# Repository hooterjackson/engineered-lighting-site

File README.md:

# Engineered Lighting · Engineering Notebook

The prototype series for the Engineered Lighting robotic spotlight — research,
bench builds, perception stack, and software — published as a book-style site.

**Live site:** <https://hooterjackson.github.io/engineered-lighting-site/>
(moving to <https://engineering.engineered.lighting> once DNS cuts over)

## Working on the site

```bash
pip install -r requirements-site.txt
mkdocs serve
```

Every push to `main` builds with `--strict` and deploys to GitHub Pages via
[`.github/workflows/publish.yml`](.github/workflows/publish.yml).

Adding a chapter: drop `09-whatever.md` (numeric prefix, H1 title, optional
`title:` front matter for the sidebar) into `docs/` — the nav picks it up
automatically; no config edits needed. A chapter that belongs in a titled
sidebar group is listed explicitly in `docs/.pages` above its `...` catch-all;
anything unlisted lands after the last group.

## The front pages

The site root and `/vision/`, `/hardware/` and `/software/` are standalone static
pages (`docs/index.html`, `docs/<page>/index.html`) built from the owner's Claude
Design handoff. MkDocs copies them through untouched, so Material's CSS and JS
never load on them. The notebook landing that used to be `/` is now `/notebook/`.

Their shared assets live in `docs/assets/site/`: `site.css` (tokens, nav, footer),
one stylesheet per page, `js/`, self-hosted IBM Plex and three.js r160, and the
large binaries listed in `large-assets.json` (apartment point clouds, the den
scan, the Vision films). A binary marked `"present": false` is never requested;
the page shows its load-error copy instead. `tools/site/den_scan.py` rebuilds the
den scan from its source pack. Images the owner has yet to supply are marked in
the HTML with `data-slot` (diagram slots also carry `data-privacy`); replace a slot
with an `` once the image is approved for publication.

Chapter `- [ ]` checklists are interactive on the site (state in the
reader's browser, keyed by page slug + item position) — reordering or
inserting checklist items in a doc shifts readers' saved checkmarks.

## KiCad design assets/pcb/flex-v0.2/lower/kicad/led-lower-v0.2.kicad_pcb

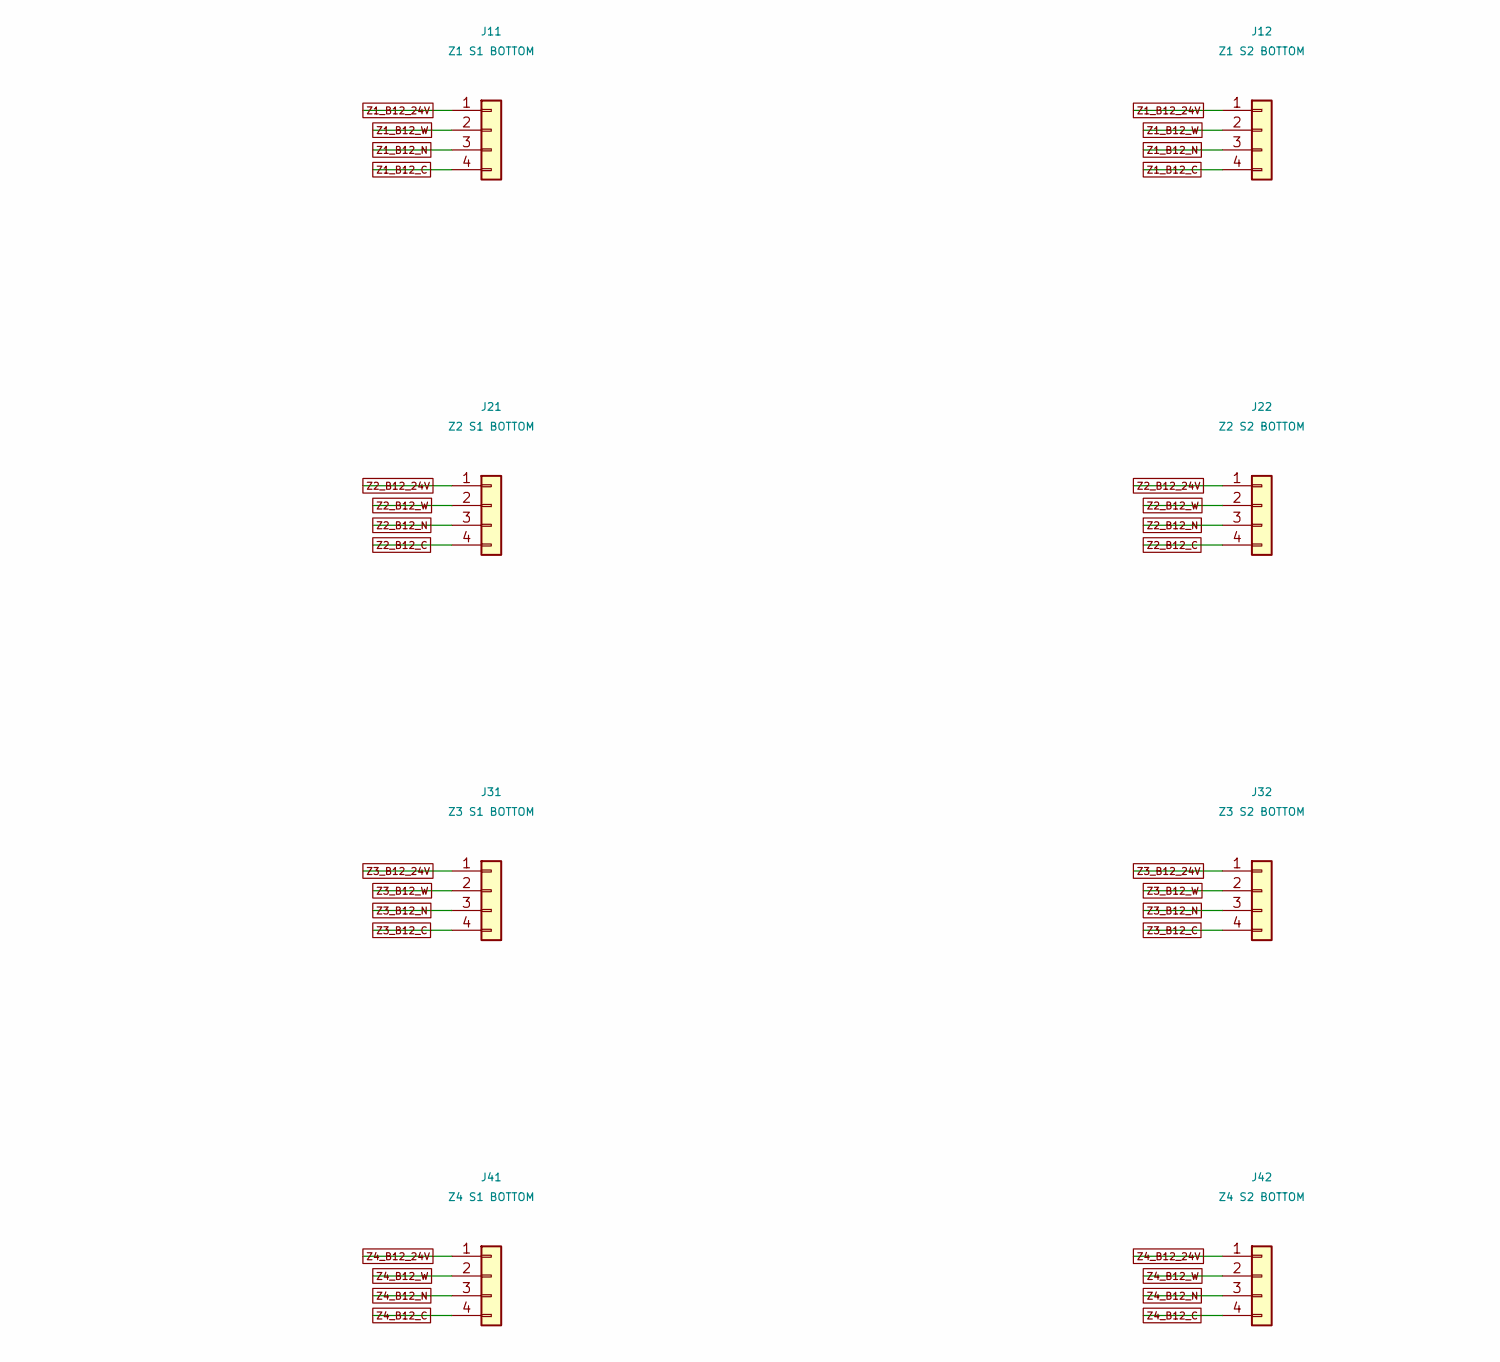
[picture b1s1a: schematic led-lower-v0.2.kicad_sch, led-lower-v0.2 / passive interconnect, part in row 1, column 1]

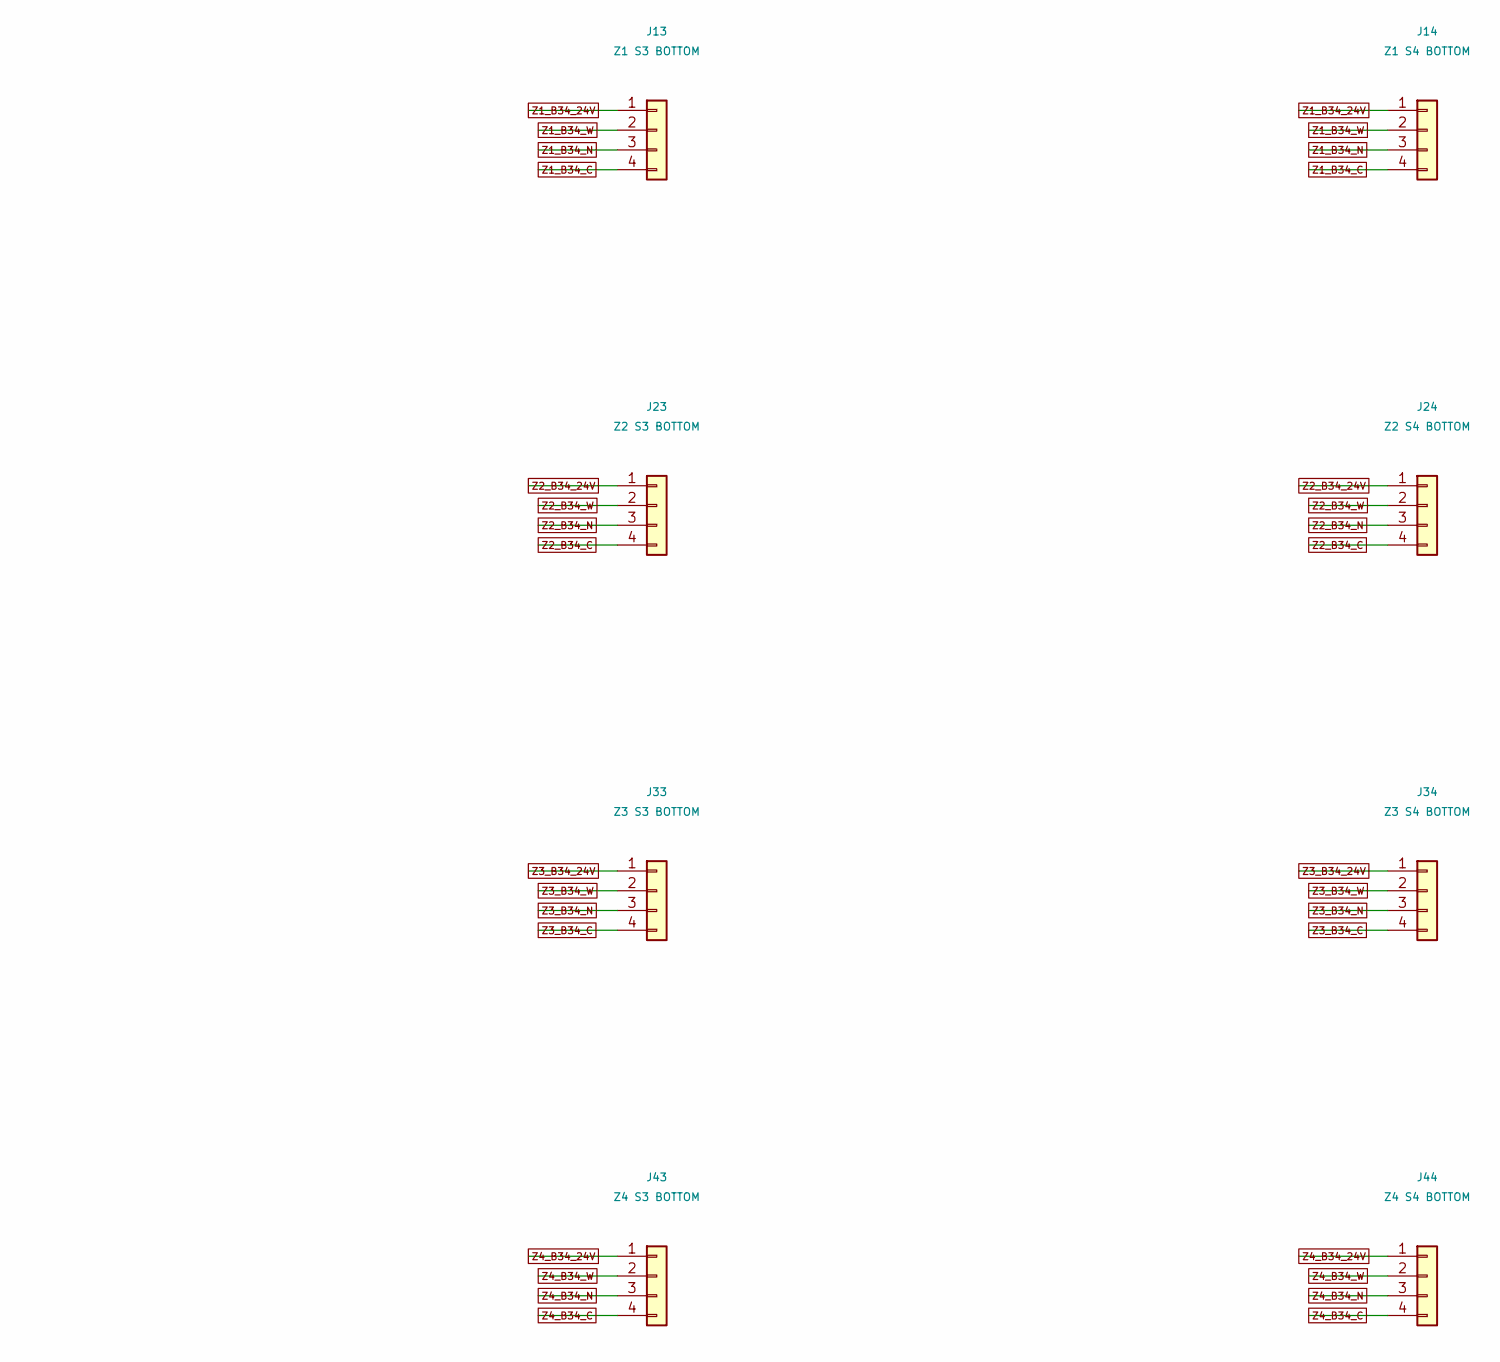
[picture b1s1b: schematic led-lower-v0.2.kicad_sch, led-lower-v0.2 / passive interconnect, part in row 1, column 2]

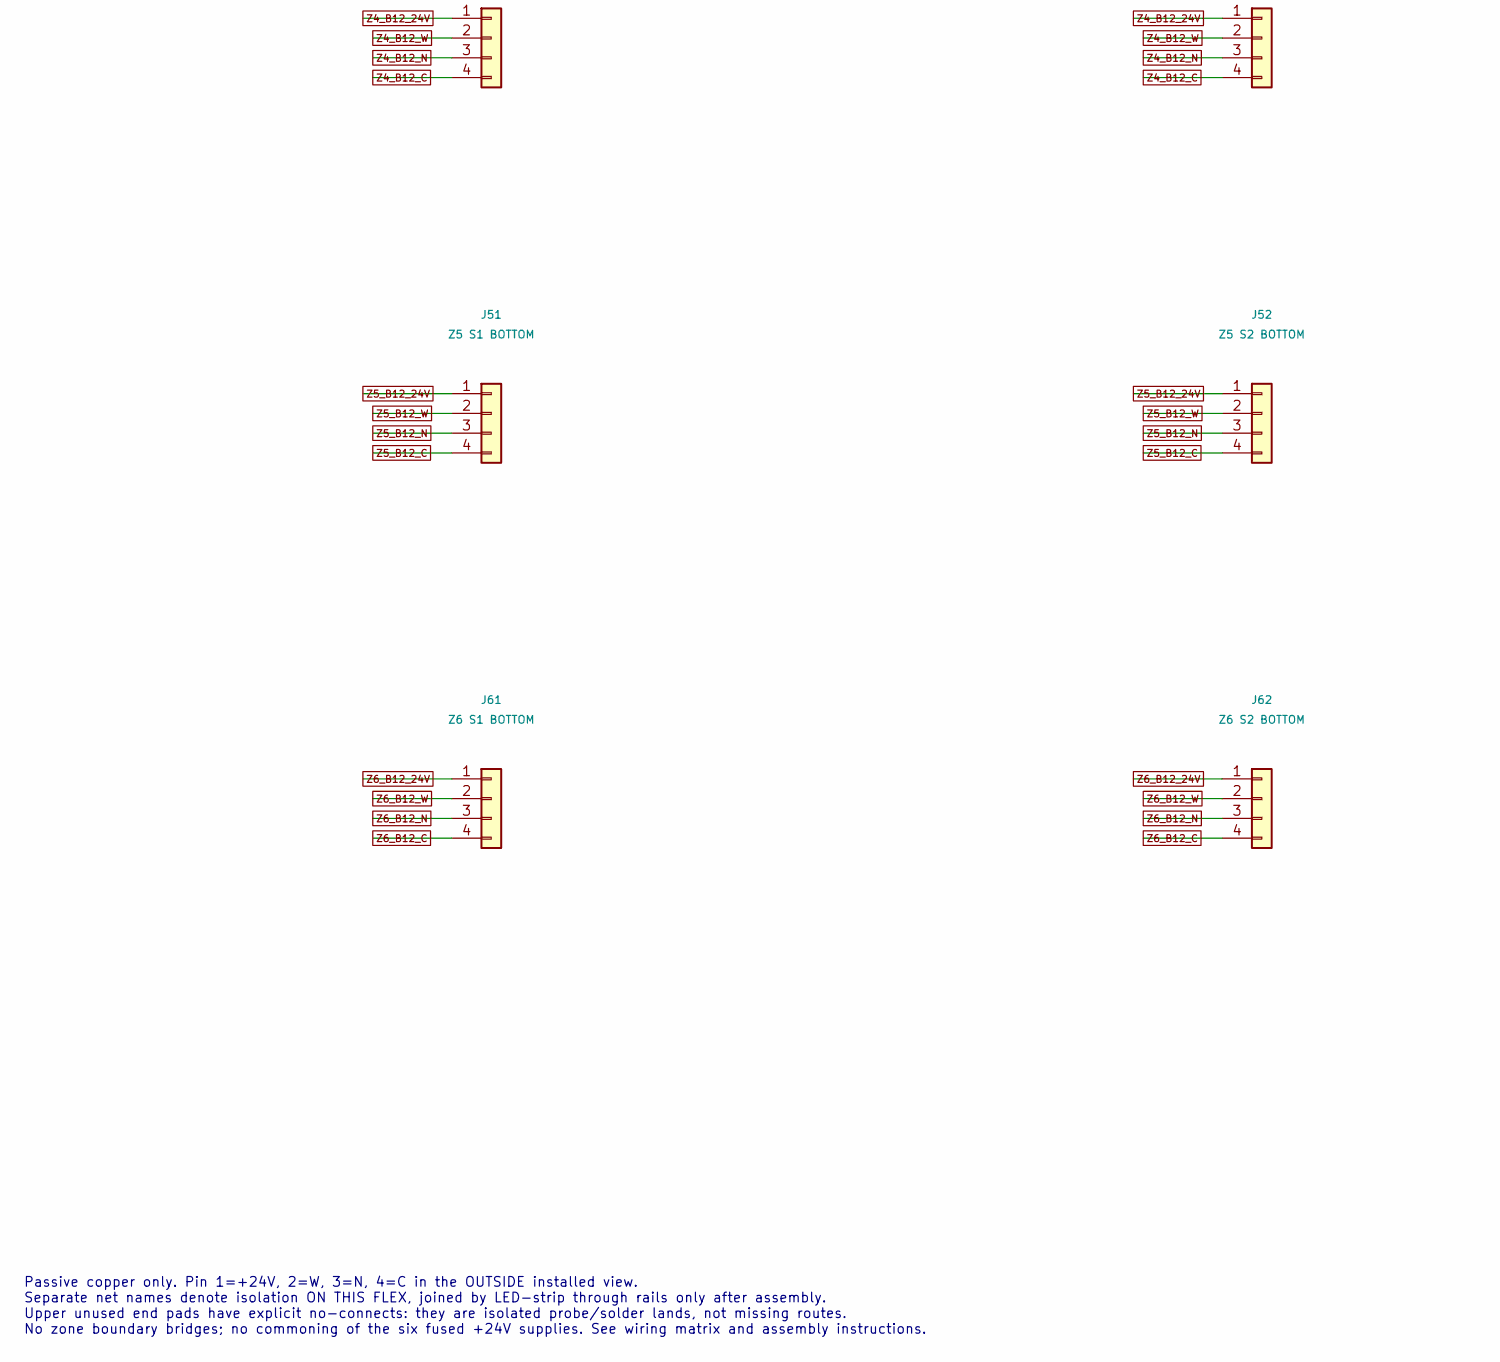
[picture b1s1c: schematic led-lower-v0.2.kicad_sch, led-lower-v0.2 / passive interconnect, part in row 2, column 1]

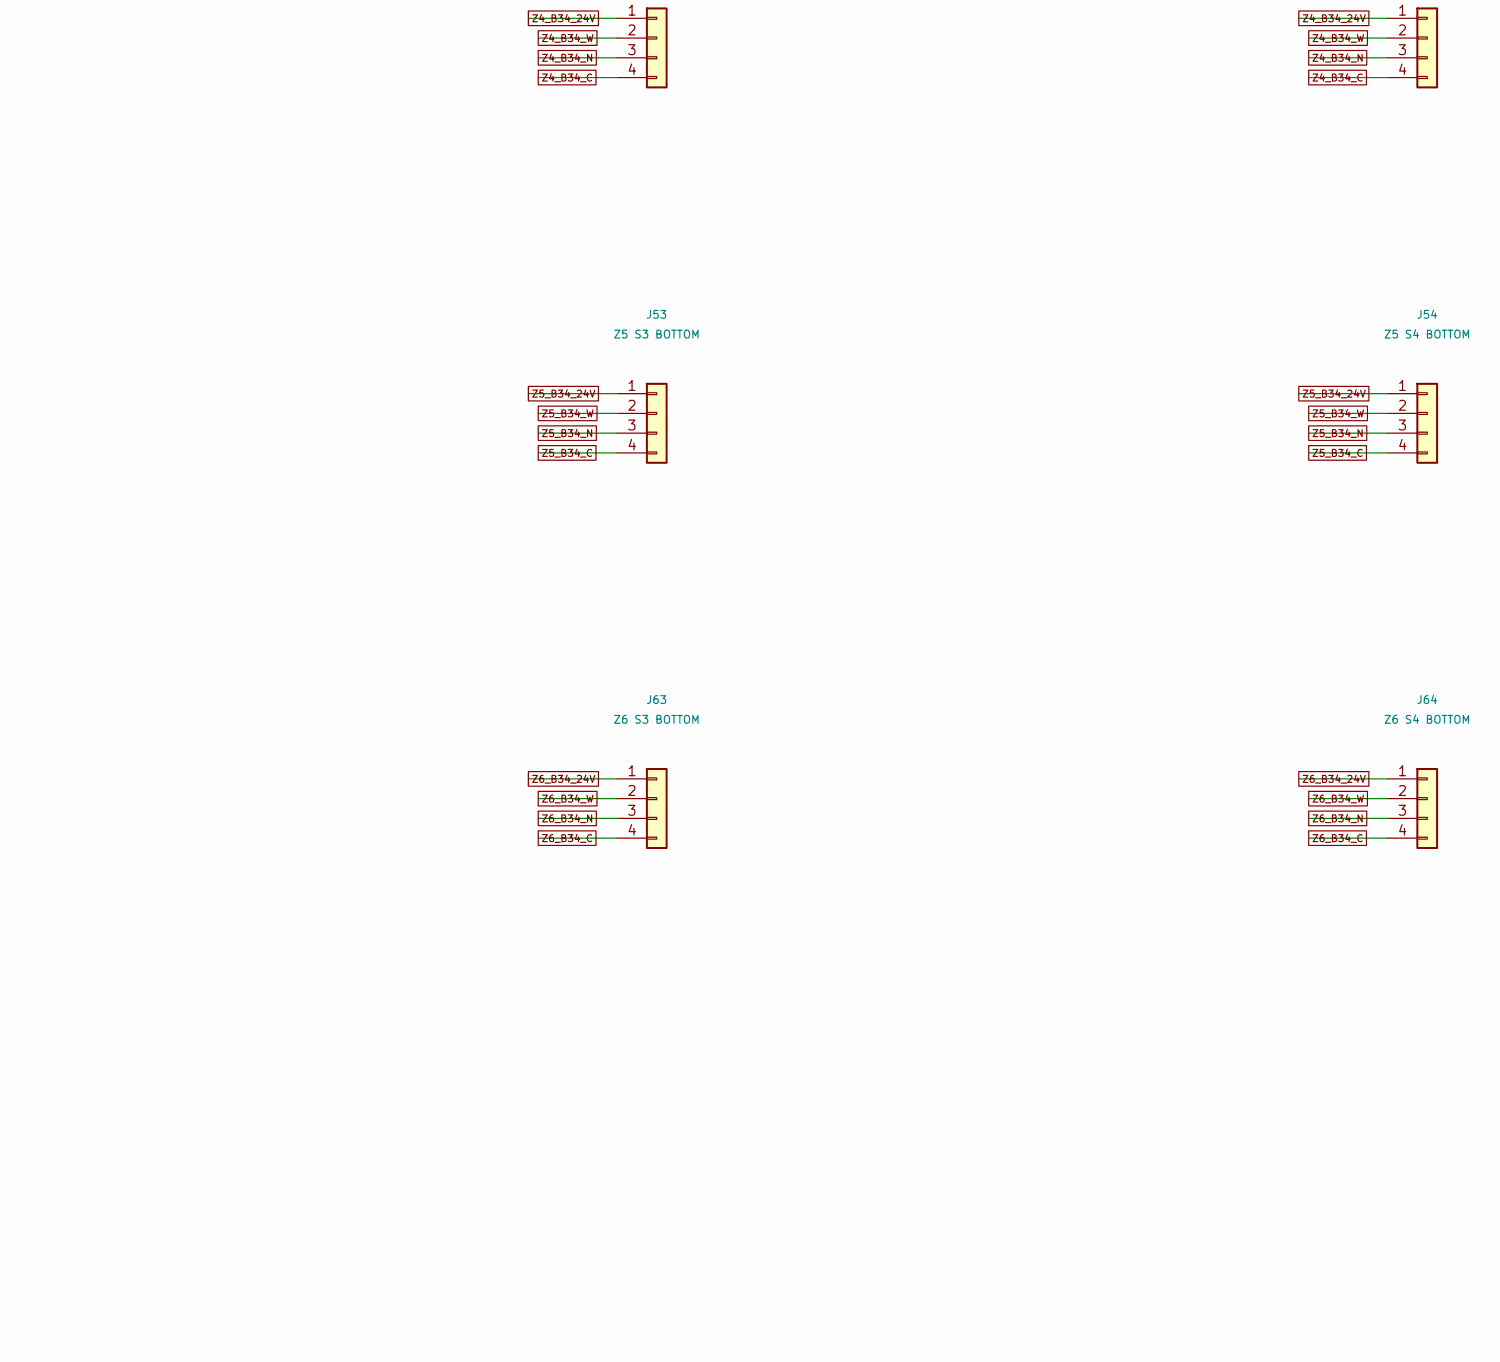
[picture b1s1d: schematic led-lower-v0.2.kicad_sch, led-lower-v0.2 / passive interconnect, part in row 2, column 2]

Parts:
J11: Z1 S1 BOTTOM; J11_Solder4
J12: Z1 S2 BOTTOM; J12_Solder4
J13: Z1 S3 BOTTOM; J13_Solder4
J14: Z1 S4 BOTTOM; J14_Solder4
J21: Z2 S1 BOTTOM; J21_Solder4
J22: Z2 S2 BOTTOM; J22_Solder4
J23: Z2 S3 BOTTOM; J23_Solder4
J24: Z2 S4 BOTTOM; J24_Solder4
J31: Z3 S1 BOTTOM; J31_Solder4
J32: Z3 S2 BOTTOM; J32_Solder4
J33: Z3 S3 BOTTOM; J33_Solder4
J34: Z3 S4 BOTTOM; J34_Solder4
J41: Z4 S1 BOTTOM; J41_Solder4
J42: Z4 S2 BOTTOM; J42_Solder4
J43: Z4 S3 BOTTOM; J43_Solder4
J44: Z4 S4 BOTTOM; J44_Solder4
J51: Z5 S1 BOTTOM; J51_Solder4
J52: Z5 S2 BOTTOM; J52_Solder4
J53: Z5 S3 BOTTOM; J53_Solder4
J54: Z5 S4 BOTTOM; J54_Solder4
J61: Z6 S1 BOTTOM; J61_Solder4
J62: Z6 S2 BOTTOM; J62_Solder4
J63: Z6 S3 BOTTOM; J63_Solder4
J64: Z6 S4 BOTTOM; J64_Solder4

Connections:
Z1_B12_24V: J11.1, J12.1
Z1_B12_C: J11.4, J12.4
Z1_B12_N: J11.3, J12.3
Z1_B12_W: J11.2, J12.2
Z1_B34_24V: J13.1, J14.1
Z1_B34_C: J13.4, J14.4
Z1_B34_N: J13.3, J14.3
Z1_B34_W: J13.2, J14.2
Z2_B12_24V: J21.1, J22.1
Z2_B12_C: J21.4, J22.4
Z2_B12_N: J21.3, J22.3
Z2_B12_W: J21.2, J22.2
Z2_B34_24V: J23.1, J24.1
Z2_B34_C: J23.4, J24.4
Z2_B34_N: J23.3, J24.3
Z2_B34_W: J23.2, J24.2
Z3_B12_24V: J31.1, J32.1
Z3_B12_C: J31.4, J32.4
Z3_B12_N: J31.3, J32.3
Z3_B12_W: J31.2, J32.2
Z3_B34_24V: J33.1, J34.1
Z3_B34_C: J33.4, J34.4
Z3_B34_N: J33.3, J34.3
Z3_B34_W: J33.2, J34.2
Z4_B12_24V: J41.1, J42.1
Z4_B12_C: J41.4, J42.4
Z4_B12_N: J41.3, J42.3
Z4_B12_W: J41.2, J42.2
Z4_B34_24V: J43.1, J44.1
Z4_B34_C: J43.4, J44.4
Z4_B34_N: J43.3, J44.3
Z4_B34_W: J43.2, J44.2
Z5_B12_24V: J51.1, J52.1
Z5_B12_C: J51.4, J52.4
Z5_B12_N: J51.3, J52.3
Z5_B12_W: J51.2, J52.2
Z5_B34_24V: J53.1, J54.1
Z5_B34_C: J53.4, J54.4
Z5_B34_N: J53.3, J54.3
Z5_B34_W: J53.2, J54.2
Z6_B12_24V: J61.1, J62.1
Z6_B12_C: J61.4, J62.4
Z6_B12_N: J61.3, J62.3
Z6_B12_W: J61.2, J62.2
Z6_B34_24V: J63.1, J64.1
Z6_B34_C: J63.4, J64.4
Z6_B34_N: J63.3, J64.3
Z6_B34_W: J63.2, J64.2

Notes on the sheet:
Passive copper only. Pin 1=+24V, 2=W, 3=N, 4=C in the OUTSIDE installed view. Separate net names denote isolation ON THIS FLEX, joined by LED-strip through rails only after assembly. Upper unused end pads have explicit no-connects: they are isolated probe/solder lands, not missing routes. No zone b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

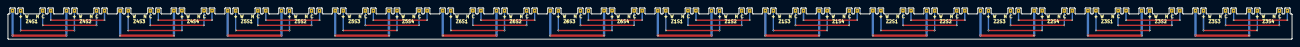
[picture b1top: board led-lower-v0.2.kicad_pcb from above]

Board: 2 copper layers, 325.0 x 7.9 mm, 24 parts (0 on the bottom side), 48 nets.
